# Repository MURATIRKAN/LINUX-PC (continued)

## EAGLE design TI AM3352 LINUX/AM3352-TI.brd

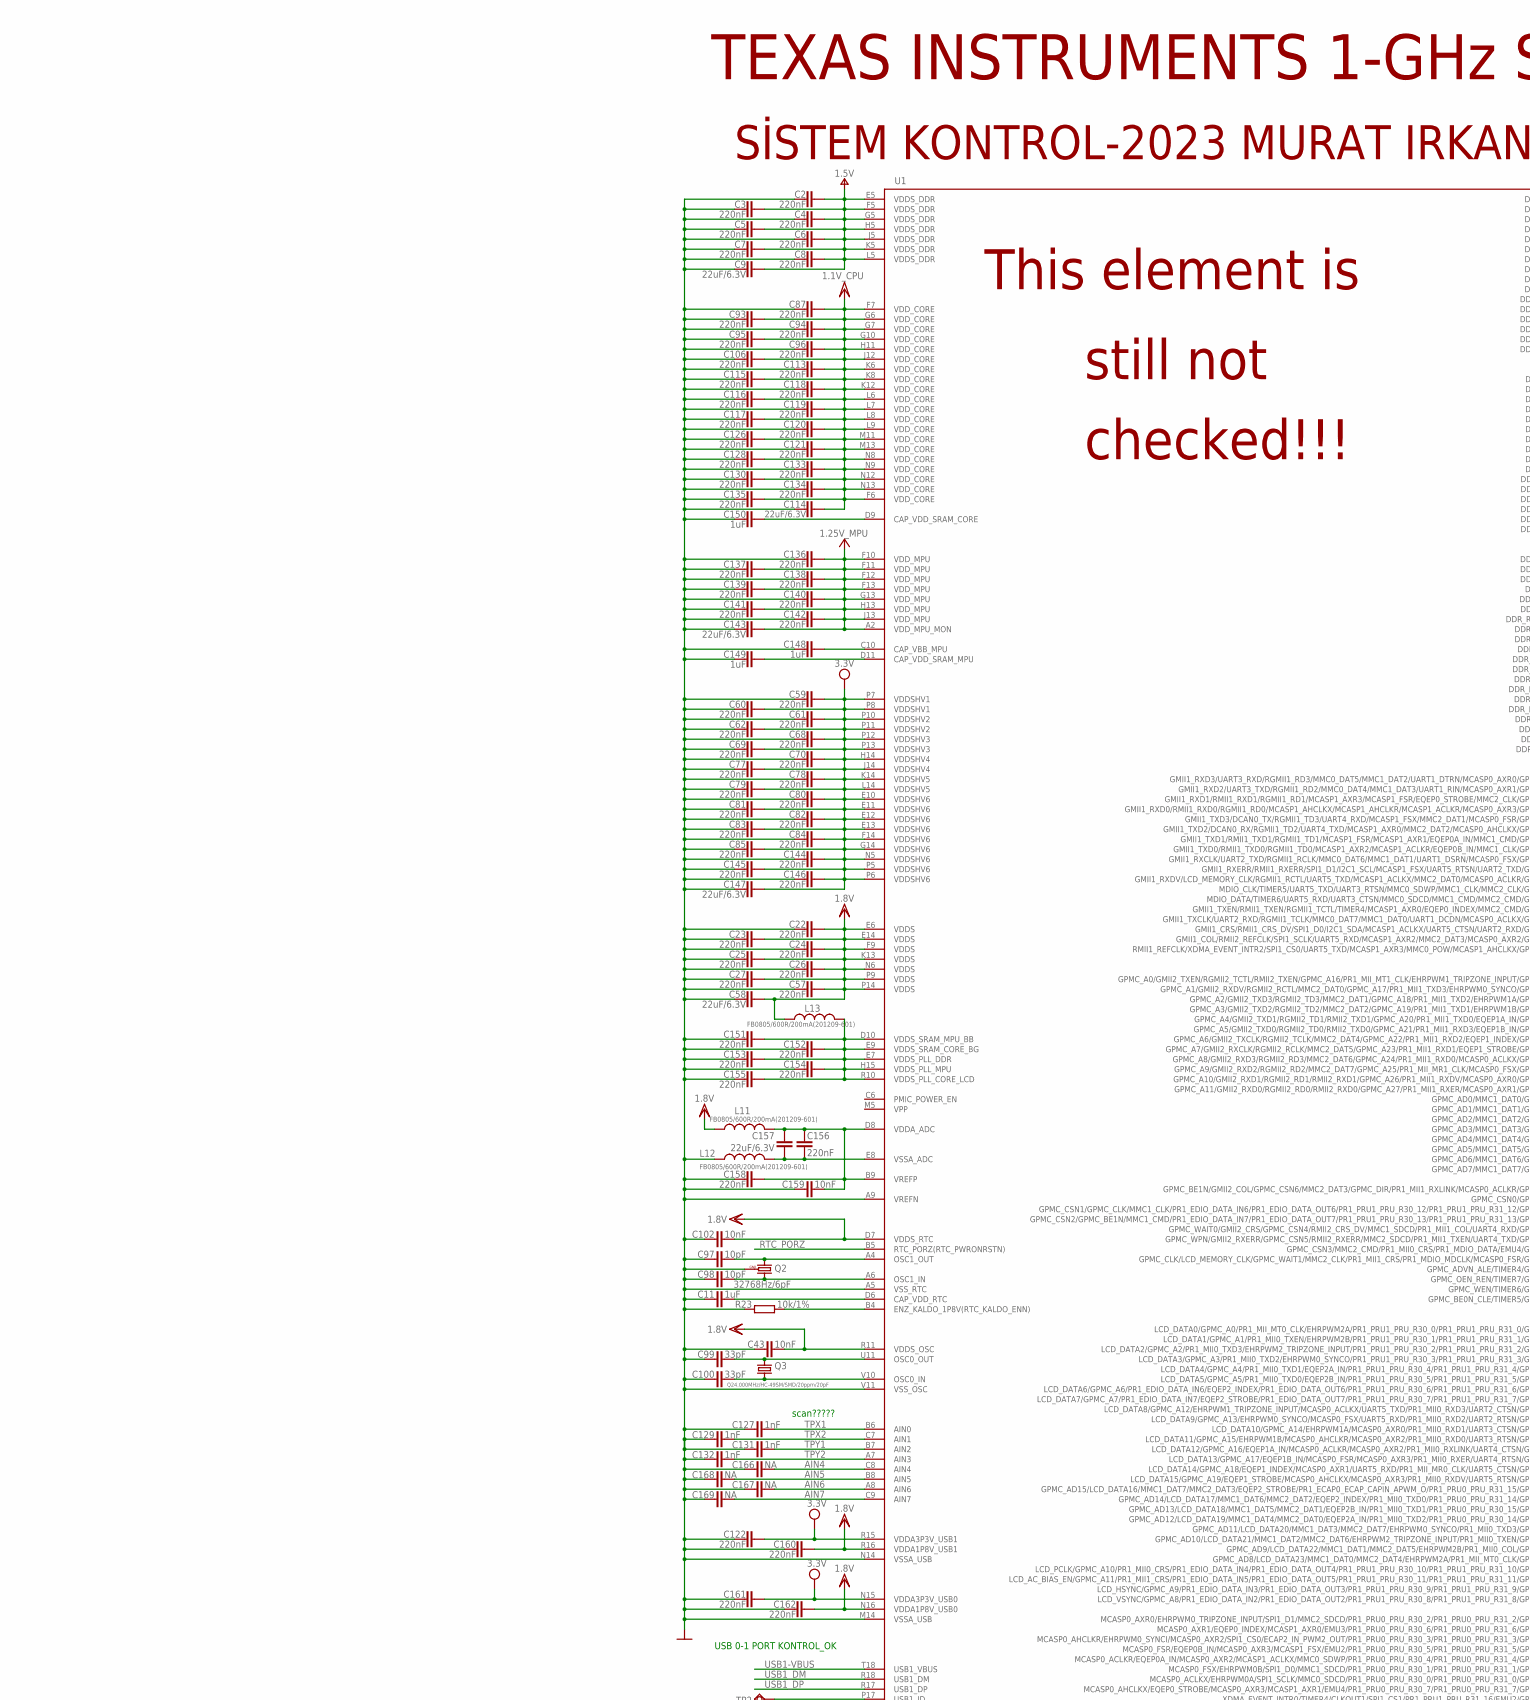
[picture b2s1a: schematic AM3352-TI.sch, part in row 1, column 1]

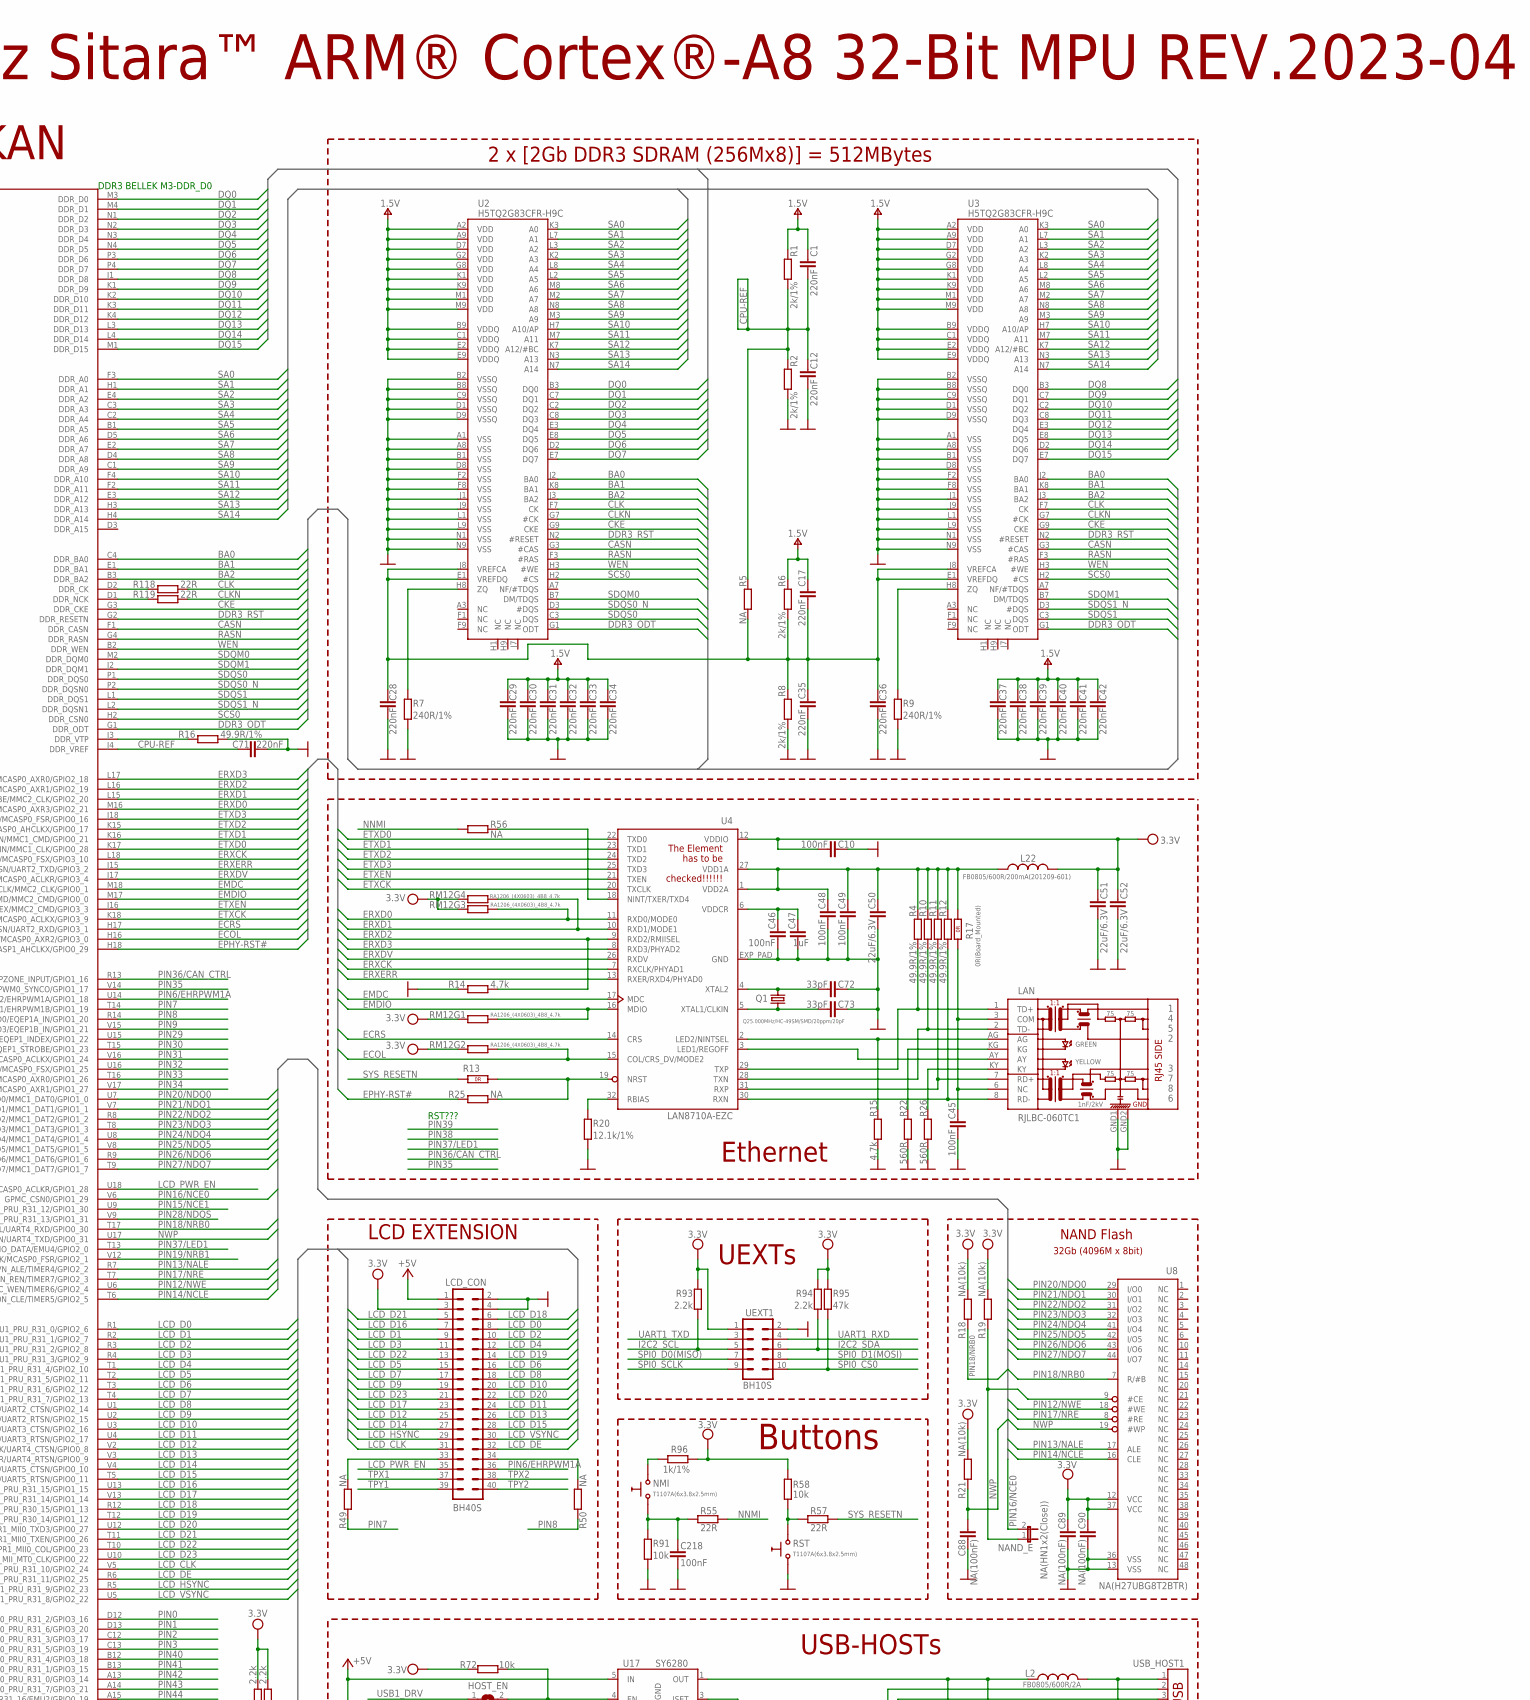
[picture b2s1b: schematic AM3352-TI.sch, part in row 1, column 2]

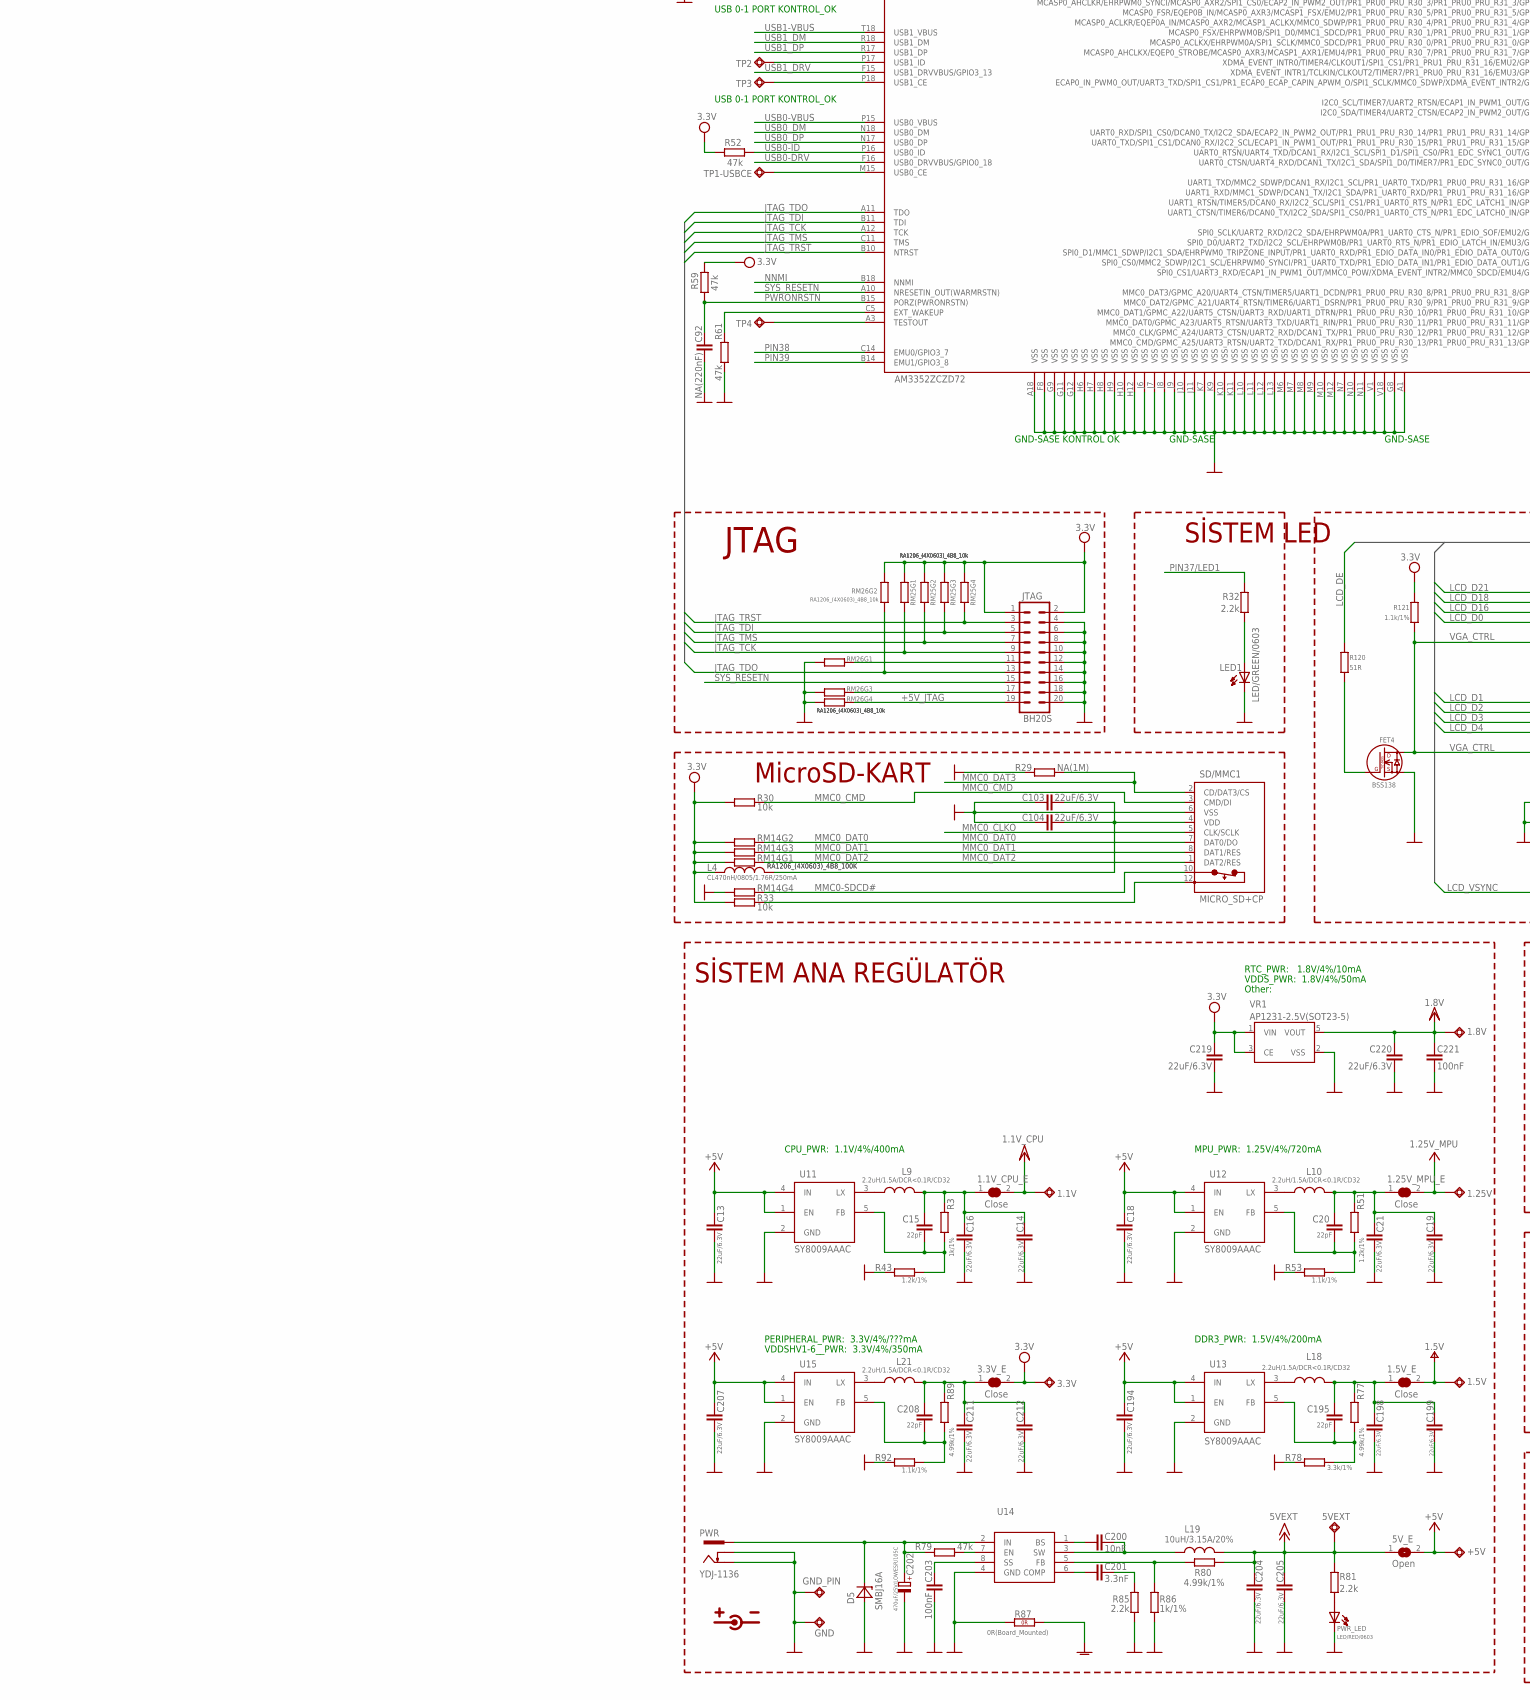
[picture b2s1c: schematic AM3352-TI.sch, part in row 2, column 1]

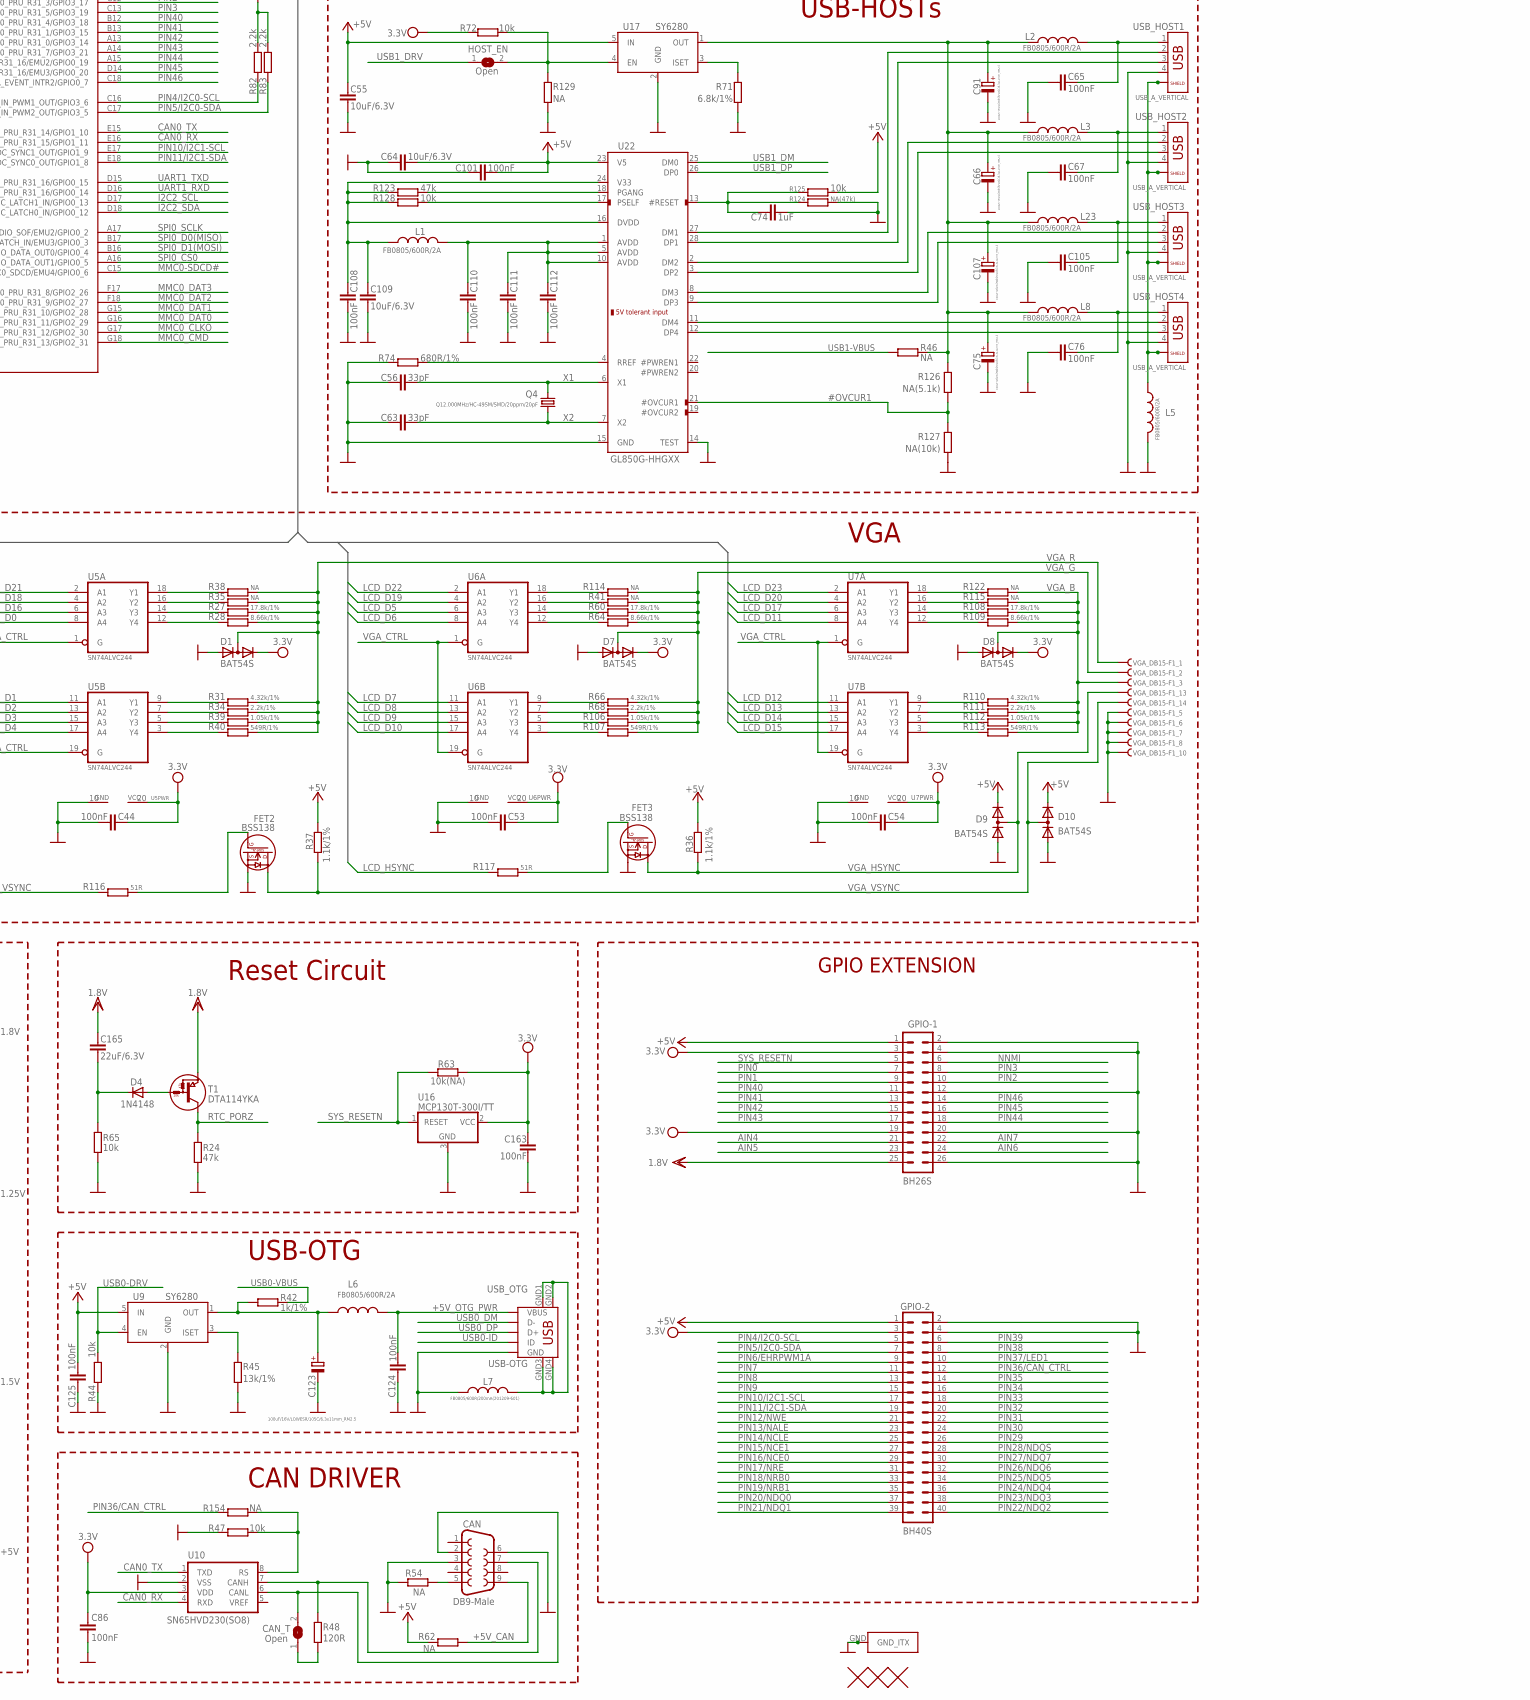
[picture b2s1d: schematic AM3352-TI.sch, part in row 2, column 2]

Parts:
1.1V, 1.5V, 1.8V, 1.25V, 3.3V, 5VEXT: TESTPADTESTPAD_40-ROUND; TESTPAD_40-ROUND
1.1V_CPU_E, 1.5V_E, 1.25V_MPU_E, 3.3V_E: Close; SJ_1_SMALLER_CLOSE
5V_E: Open; SJ_1_SMALLER
+5V: TESTPADTESTPAD_40-ROUND; TESTPAD_40-ROUND
C1, C2, C3, C4, C5, C6, C7, C8, C12, C17, C22, C23, C24, C25, C26, C27, C28, C29, C30, C31, C32, C33, C34, C35, C36, C37, C38, C39, C40, C41, C42, C57, C59, C60, C61, C62, C68, C69, C70, C71, C77, C78, C79, C80, C81, C82, C83, C84, C85, C87, C93, C94, C95, C96, C106, C113, C115, C116, C117, C118, C119, C120, C121, C122, C126, C128, C130, C133, C134, C135, C136, C137, C138, C139, C140, C141, C142, C144, C145, C146, C151, C152, C153, C154, C155, C156, C158, C160, C161, C162: 220nF; C0603_DWS
C9, C13, C14, C16, C18, C19, C21, C50, C51, C52, C58, C103, C104, C114, C143, C147, C157, C165, C194, C198, C199, C204, C205, C207, C211, C212, C219, C220: 22uF/6.3V; C0603_DWS
C10, C44, C45, C46, C48, C49, C53, C54, C65, C67, C76, C86, C101, C105, C108, C110, C111, C112, C124, C125, C163, C203, C218, C221: 100nF; C0603_DWS
C11, C47, C74, C148, C149, C150: 1uF; C0603_DWS
C15, C20, C195, C208: 22pF; C0603_DWS
C43, C102, C159, C200: 10nF; C0603_DWS
C55, C64, C109: 10uF/6.3V; C0603_DWS
C56, C63, C72, C73, C99, C100: 33pF; C0603_DWS
C66, C75, C91, C107, C123: 100uF/16V/LOWESR/105C/6.3x11mm_RM2.5; E2,5-6,3
C88, C89, C90: NA(100nF); C0603_DWS
C92: NA(220nF); C0603_DWS
C97, C98: 10pF; C0603_DWS
C127, C129, C131, C132: 1nF; C0603_DWS
C166, C167, C168, C169: NA; C0603_DWS
C201: 3.3nF; C0603_DWS
C202: 470uF/25V/LOWESR/105C; E5-10,5
CAN: DB9-Male; F09HP-MALE
CAN_T: Open; SJ
D1, D7, D8, D9, D10: BAT54S; SOT23C(BAT54S)
D4: 1N4148; MELF-MLL41
D5: SMBJ16A; DO214AA
FET2, FET3, FET4: BSS138; SOT23
GND: TESTPADTESTPAD_40-ROUND; TESTPAD_40-ROUND
GND_PIN: TESTPAD3; TEST_PAD40/70/SQUARE
GPIO-1: BH26S; ML26
GPIO-2: BH40S; ML40
HOST_EN: Open; SJ_1_SMALLER
JTAG: BH20S; ML20-MALE
L1, L2, L3, L5, L6, L8, L23: FB0805/600R/2A; L0805_5MIL_DWS
L4: CL470nH/0805/1.76R/250mA; L0805_5MIL_DWS
L7, L11, L12, L13, L22: FB0805/600R/200mA(201209-601); L0805_5MIL_DWS
L9, L10, L18, L21: 2.2uH/1.5A/DCR<0.1R/CD32; CD32
L19: 10uH/3.15A/20%; 8X8MM_3131
LAN: RJLBC-060TC1
LCD_CON: BH40S; ML40
LED1: LED/GREEN/0603; LED-0603
NAND_E: NA(HN1x2(Close)); JP1
NMI: T1107A(6x3.8x2.5mm); SW-TAKT_6X3.5_SMD
PWR: YDJ-1136; PWR_JACK_UNI_MILLING
PWR_LED: LED/RED/0603; LED-0603
Q1: Q25.000MHz/HC-49SM/SMD/20ppm/20pF; HC49/SMD2_THIN
Q2: 32768Hz/6pF; TC26H_3_REPAIR_SMD
Q3: Q24.000MHz/HC-49SM/SMD/20ppm/20pF; HC49/SMD2_THIN
Q4: Q12.000MHz/HC-49SM/SMD/20ppm/20pF; HC49/SMD2_THIN
R1, R2, R6, R8: 2k/1%; R0603_5MIL_DWS
R3, R42, R86, R96: 1k/1%; R0603_5MIL_DWS
R4, R10, R11, R12, R16: 49.9R/1%; R0603_5MIL_DWS
R5, R25, R35, R38, R41, R46, R49, R50, R56, R114, R115, R122, R129: NA; R0603_5MIL_DWS
R7, R9: 240R/1%; R0603_5MIL_DWS
R13: R_0R0R(NA); 0603_0R
R14, R15: 4.7k; R0603_5MIL_DWS
R17, R87: 0R(Board_Mounted); 0603_0R
R18, R19, R21, R127: NA(10k); R0603_5MIL_DWS
R20: 12.1k/1%; R0603_5MIL_DWS
R22, R26: 560R; R0603_5MIL_DWS
R23: 10k/1%; R0603_5MIL_DWS
R24, R52, R59, R61, R79, R95, R123: 47k; R0603_5MIL_DWS
R27, R60, R108: 17.8k/1%; R0603_5MIL_DWS
R28, R64, R109: 8.66k/1%; R0603_5MIL_DWS
R29: NA(1M); R0603_5MIL_DWS
R30, R33, R44, R47, R58, R65, R72, R91, R125, R128: 10k; R0603_5MIL_DWS
R31, R66, R110: 4.32k/1%; R0603_5MIL_DWS
R32, R81, R82, R83, R85, R93, R94: 2.2k; R0603_5MIL_DWS
R34, R68, R111: 2.2k/1%; R0603_5MIL_DWS
R36, R37, R53, R92, R121: 1.1k/1%; R0603_5MIL_DWS
R39, R106, R112: 1.05k/1%; R0603_5MIL_DWS
R40, R107, R113: 549R/1%; R0603_5MIL_DWS
R43, R51: 1.2k/1%; R0603_5MIL_DWS
R45: 13k/1%; R0603_5MIL_DWS
R48: 120R; R1206_5MIL_WS
R54, R62, R154: NA; R0603_5MIL_DWS_NA
R55, R57, R118, R119: 22R; R0603_5MIL_DWS
R63: 10k(NA); R0603_5MIL_DWS
R71: 6.8k/1%; R0603_5MIL_DWS
R74: 680R/1%; R0603_5MIL_DWS
R77, R80, R89: 4.99k/1%; R0603_5MIL_DWS
R78: 3.3k/1%; R0603_5MIL_DWS
R116, R117, R120: 51R; R0603_5MIL_DWS
R124: NA(47k); R0603_5MIL_DWS
R126: NA(5.1k); R0603_5MIL_DWS
RM12: RA1206_(4X0603)_4B8_4.7k; R_MATRIX_4
RM14: RA1206_(4X0603)_4B8_100K; R_MATRIX_4
RM25, RM26: RA1206_(4X0603)_4B8_10k; R_MATRIX_4
RST: T1107A(6x3.8x2.5mm); SW-TAKT_6X3.5_SMD
SD/MMC1: MICRO_SD+CP; TFR-MEM-CON
T1: DTA114YKA; SOT-23
TP1-USBCE, TP2, TP3, TP4: TESTPADTESTPAD_40-ROUND; TESTPAD_40-ROUND
U1: AM3352ZCZD72; S-PBGA-N324
U2, U3: H5TQ2G83CFR-H9C; FBGA78
U4: LAN8710A-EZC; QFN-32
U5, U6, U7: SN74ALVC244; PW
U8: NA(H27UBG8T2BTR); TSOP48
U9, U17: SY6280; SOT23-5
U10: SN65HVD230(SO8); SO-08
U11, U12, U13, U15: SY8009AAAC; SOT23-5
U14: MP1482DS; SOIC8
U16: MCP130T-300I/TT; SOT23
U19, U20, U21: FIDUCIAL1X2; FIDUCIAL-1X2
U22: GL850G-HHGXX; SSOP28
U$1: NANO_ITX_; NANO-ITX_140X140
UEXT1: BH10S; ML10-MALE
USB_HOST1, USB_HOST2, USB_HOST3, USB_HOST4: USB_A_VERTICAL; USB_A_VERTICAL_PTH
USB_OTG: USB-OTG; USB_MINI_9PIN
VGA_DB15-F1: VGA15; DB15-F_22MM
VR1: AP1231-2.5V(SOT23-5); SOT-23-5

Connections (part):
#OVCUR1: R126.1, R127.2, U22.21 (#OVCUR1)
+5V: 5V_E.2, +5V.1, C13.1, C18.1, C55.1, C64.1, C101.1, C125.1, C194.1, C207.1, D9.2 (K), D10.2 (K), GPIO-1.1, GPIO-2.1, LCD_CON.1, R36.2, R37.2, R62.1, R125.2, U9.5 (IN), U11.1 (EN), U11.4 (IN), U12.1 (EN), U12.4 (IN), U13.1 (EN), U13.4 (IN), U15.1 (EN), U15.4 (IN), U17.5 (IN), U22.23 (V5)
+5V_CAN: CAN.9, R62.2
+5V_JTAG: JTAG.19, RM26.4.2 (2)
+5V_OTG_PWR: C124.1, L6.1, USB_OTG.VBUS
+15V: 5VEXT.1, 5V_E.1, C204.1, C205.1, L19.2, R80.2, R81.1
AIN4: C166.2, GPIO-1.21, U1.C8 (AIN4)
AIN5: C168.2, GPIO-1.23, U1.B8 (AIN5)
AIN6: C167.2, GPIO-1.24, U1.A8 (AIN6)
AIN7: C169.2, GPIO-1.22, U1.C9 (AIN7)
AVDD1: C110.1, C111.1, C112.1, L1.2, U22.1 (AVDD), U22.5 (AVDD), U22.10 (AVDD)
BA0: U1.C4 (DDR_BA0), U2.J2 (BA0), U3.J2 (BA0)
BA1: U1.E1 (DDR_BA1), U2.K8 (BA1), U3.K8 (BA1)
BA2: U1.B3 (DDR_BA2), U2.J3 (BA2), U3.J3 (BA2)
CAN0_RX: U1.E16 (UART0_TXD/SPI1_CS1/DCAN0_RX/I2C2_SCL/EC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), U10.4 (RXD)
CAN0_TX: U1.E15 (UART0_RXD/SPI1_CS0/DCAN0_TX/I2C2_SDA/EC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), U10.1 (TXD)
CANH: CAN.7, R48.2, U10.7 (CANH)
CANL: CAN.2, CAN_T.2, U10.6 (CANL)
CASN: U1.F1 (DDR_CASN), U2.G3 (#CAS), U3.G3 (#CAS)
CKE: U1.G3 (DDR_CKE), U2.G9 (CKE), U3.G9 (CKE)
CLK: R118.1, U2.F7 (CK), U3.F7 (CK)
CLKN: R119.1, U2.G7 (#CK), U3.G7 (#CK)
CPU-REF: C1.2, C12.2, C71.2, R1.1, R2.2, R5.2, U1.J4 (DDR_VREF)
DDR3_ODT: U1.G1 (DDR_ODT), U2.G1 (ODT), U3.G1 (ODT)
DDR3_RST: U1.G2 (DDR_RESETN), U2.N2 (#RESET), U3.N2 (#RESET)
DM1: U22.27 (DM1), USB_HOST1.2
DM2: U22.2 (DM2), USB_HOST2.2
DM3: U22.8 (DM3), USB_HOST3.2
DM4: U22.11 (DM4), USB_HOST4.2
DP1: U22.28 (DP1), USB_HOST1.3
DP2: U22.3 (DP2), USB_HOST2.3
DP3: U22.9 (DP3), USB_HOST3.3
DP4: U22.12 (DP4), USB_HOST4.3
DQ0: U1.M3 (DDR_D0), U2.B3 (DQ0)
DQ1: U1.M4 (DDR_D1), U2.C7 (DQ1)
DQ2: U1.N1 (DDR_D2), U2.C2 (DQ2)
DQ3: U1.N2 (DDR_D3), U2.C8 (DQ3)
DQ4: U1.N3 (DDR_D4), U2.E3 (DQ4)
DQ5: U1.N4 (DDR_D5), U2.E8 (DQ5)
DQ6: U1.P3 (DDR_D6), U2.D2 (DQ6)
DQ7: U1.P4 (DDR_D7), U2.E7 (DQ7)
DQ8: U1.J1 (DDR_D8), U3.B3 (DQ0)
DQ9: U1.K1 (DDR_D9), U3.C7 (DQ1)
DQ10: U1.K2 (DDR_D10), U3.C2 (DQ2)
DQ11: U1.K3 (DDR_D11), U3.C8 (DQ3)
DQ12: U1.K4 (DDR_D12), U3.E3 (DQ4)
DQ13: U1.L3 (DDR_D13), U3.E8 (DQ5)
DQ14: U1.L4 (DDR_D14), U3.D2 (DQ6)
DQ15: U1.M1 (DDR_D15), U3.E7 (DQ7)
DRAM-REF: C17.2, C28.2, C35.2, C36.2, R5.1, R6.1, R8.2, U2.E1 (VREFDQ), U2.J8 (VREFCA), U3.E1 (VREFDQ), U3.J8 (VREFCA)
DVDD1: C108.1, C109.1, L1.1, R123.1, R128.1, U22.16 (DVDD), U22.24 (V33)
ECOL: RM12.2.2 (2), U1.H16 (GMII1_COL/RMII2_REFCLK/SPI1_SCLK/UART5_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), U4.15 (COL/CRS_DV/MODE2)
ECRS: U1.H17 (GMII1_CRS/RMII1_CRS_DV/SPI1_D0/I2C1_SDA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), U4.14 (CRS)
EMDC: U1.M18 (MDIO_CLK/TIMER5/UART5_TXD/UART3_RTSN/MM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), U4.17 (MDC)
EMDIO: RM12.1.2 (2), U1.M17 (MDIO_DATA/TIMER6/UART5_RXD/UART3_CTSN/M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), U4.16 (MDIO)
EPHY-RST#: R25.1, U1.H18 (RMII1_REFCLK/XDMA_EVENT_INTR2/SPI1_CS0/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)
ERXCK: U1.L18 (GMII1_RXCLK/UART2_TXD/RGMII1_RCLK/MMC0_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), U4.7 (RXCLK/PHYAD1)
ERXD0: RM12.3.2 (2), U1.M16 (GMII1_RXD0/RMII1_RXD0/RGMII1_RD0/MCASP1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), U4.11 (RXD0/MODE0)
ERXD1: RM12.4.2 (2), U1.L15 (GMII1_RXD1/RMII1_RXD1/RGMII1_RD1/MCASP1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), U4.10 (RXD1/MODE1)
ERXD2: R14.2, U1.L16 (GMII1_RXD2/UART3_TXD/RGMII1_RD2/MMC0_DA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), U4.9 (RXD2/RMIISEL)
ERXD3: U1.L17 (GMII1_RXD3/UART3_RXD/RGMII1_RD3/MMC0_DA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), U4.8 (RXD3/PHYAD2)
ERXDV: U1.J17 (GMII1_RXDV/LCD_MEMORY_CLK/RGMII1_RCTL/U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), U4.26 (RXDV)
ERXERR: U1.J15 (GMII1_RXERR/RMII1_RXERR/SPI1_D1/I2C1_SC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), U4.13 (RXER/RXD4/PHYAD0)
ETXCK: U1.K18 (GMII1_TXCLK/UART2_RXD/RGMII1_TCLK/MMC0_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), U4.20 (TXCLK)
ETXD0: U1.K17 (GMII1_TXD0/RMII1_TXD0/RGMII1_TD0/MCASP1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), U4.22 (TXD0)
ETXD1: U1.K16 (GMII1_TXD1/RMII1_TXD1/RGMII1_TD1/MCASP1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), U4.23 (TXD1)
ETXD2: U1.K15 (GMII1_TXD2/DCAN0_RX/RGMII1_TD2/UART4_TX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), U4.24 (TXD2)
ETXD3: U1.J18 (GMII1_TXD3/DCAN0_TX/RGMII1_TD3/UART4_RX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), U4.25 (TXD3)
ETXEN: U1.J16 (GMII1_TXEN/RMII1_TXEN/RGMII1_TCTL/TIMER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), U4.21 (TXEN)
GND: C2.1, C3.1, C4.1, C5.1, C6.1, C7.1, C8.1, C9.1, C10.1, C11.1, C12.1, C13.2, C14.2, C16.2, C18.2, C19.2, C21.2, C22.1, C23.1, C24.1, C25.1, C26.1, C27.1, C28.1, C29.1, C30.1, C31.1, C32.1, C33.1, C34.1, C35.1, C36.1, C37.1, C38.1, C39.1, C40.1, C41.1, C42.1, C43.1, C44.2, C45.1, C46.1, C47.1, C48.1, C49.1, C50.1, C51.1, C52.1, C53.2, C54.2, C55.2, C56.1, C57.1, C58.1, C59.1, C60.1, C61.1, C62.1, C63.1, C64.2, C65.2, C66.-, C67.2, C68.1, C69.1, C70.1, C71.1, C72.1, C73.1, C74.1, C75.-, C76.2, C77.1, C78.1, C79.1, C80.1, C81.1, C82.1, C83.1, C84.1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
GNDA: R87.2 (1.2)
I2C2_SCL: R93.1, U1.D17 (UART1_RTSN/TIMER5/DCAN0_RX/I2C2_SCL/SPI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), UEXT1.5
I2C2_SDA: R94.1, U1.D18 (UART1_CTSN/TIMER6/DCAN0_TX/I2C2_SDA/SPI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), UEXT1.6
JTAG_TCK: JTAG.9, RM25.1.1 (1), U1.A12 (TCK)
JTAG_TDI: JTAG.5, RM25.3.1 (1), U1.B11 (TDI)
JTAG_TDO: JTAG.13, RM26.2.2 (2), U1.A11 (TDO)
JTAG_TMS: JTAG.7, RM25.2.1 (1), U1.C11 (TMS)
JTAG_TRST: JTAG.3, RM25.4.1 (1), U1.B10 (NTRST)
LCD_CLK: LCD_CON.31, U1.V5 (LCD_PCLK/GPMC_A10/PR1_MII0_CRS/PR1_EDIO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)
LCD_D0: LCD_CON.8, U1.R1 (LCD_DATA0/GPMC_A0/PR1_MII_MT0_CLK/EHRPW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), U5.8 (A4)
LCD_D1: LCD_CON.9, U1.R2 (LCD_DATA1/GPMC_A1/PR1_MII0_TXEN/EHRPWM2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), U5.11 (A1)
LCD_D2: LCD_CON.10, U1.R3 (LCD_DATA2/GPMC_A2/PR1_MII0_TXD3/EHRPWM2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), U5.13 (A2)
LCD_D3: LCD_CON.11, U1.R4 (LCD_DATA3/GPMC_A3/PR1_MII0_TXD2/EHRPWM0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), U5.15 (A3)
LCD_D4: LCD_CON.12, U1.T1 (LCD_DATA4/GPMC_A4/PR1_MII0_TXD1/EQEP2A_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), U5.17 (A4)
LCD_D5: LCD_CON.15, U1.T2 (LCD_DATA5/GPMC_A5/PR1_MII0_TXD0/EQEP2B_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), U6.6 (A3)
LCD_D6: LCD_CON.16, U1.T3 (LCD_DATA6/GPMC_A6/PR1_EDIO_DATA_IN6/EQE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), U6.8 (A4)
LCD_D7: LCD_CON.17, U1.T4 (LCD_DATA7/GPMC_A7/PR1_EDIO_DATA_IN7/EQE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), U6.11 (A1)
LCD_D8: LCD_CON.18, U1.U1 (LCD_DATA8/GPMC_A12/EHRPWM1_TRIPZONE_INP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), U6.13 (A2)
LCD_D9: LCD_CON.19, U1.U2 (LCD_DATA9/GPMC_A13/EHRPWM0_SYNCO/MCASP0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), U6.15 (A3)
LCD_D10: LCD_CON.20, U1.U3 (LCD_DATA10/GPMC_A14/EHRPWM1A/MCASP0_AXR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), U6.17 (A4)
LCD_D11: LCD_CON.24, U1.U4 (LCD_DATA11/GPMC_A15/EHRPWM1B/MCASP0_AHC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), U7.8 (A4)
LCD_D12: LCD_CON.25, U1.V2 (LCD_DATA12/GPMC_A16/EQEP1A_IN/MCASP0_AC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), U7.11 (A1)
LCD_D13: LCD_CON.26, U1.V3 (LCD_DATA13/GPMC_A17/EQEP1B_IN/MCASP0_FS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), U7.13 (A2)
LCD_D14: LCD_CON.27, U1.V4 (LCD_DATA14/GPMC_A18/EQEP1_INDEX/MCASP0_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), U7.15 (A3)
LCD_D15: LCD_CON.28, U1.T5 (LCD_DATA15/GPMC_A19/EQEP1_STROBE/MCASP0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), U7.17 (A4)
LCD_D16: LCD_CON.7, U1.U13 (GPMC_AD15/LCD_DATA16/MMC1_DAT7/MMC2_DAT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), U5.6 (A3)
LCD_D17: LCD_CON.23, U1.V13 (GPMC_AD14/LCD_DATA17/MMC1_DAT6/MMC2_DAT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), U7.6 (A3)
LCD_D18: LCD_CON.6, U1.R12 (GPMC_AD13/LCD_DATA18/MMC1_DAT5/MMC2_DAT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), U5.4 (A2)
LCD_D19: LCD_CON.14, U1.T12 (GPMC_AD12/LCD_DATA19/MMC1_DAT4/MMC2_DAT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), U6.4 (A2)
LCD_D20: LCD_CON.22, U1.U12 (GPMC_AD11/LCD_DATA20/MMC1_DAT3/MMC2_DAT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), U7.4 (A2)
LCD_D21: LCD_CON.5, U1.T11 (GPMC_AD10/LCD_DATA21/MMC1_DAT2/MMC2_DAT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), U5.2 (A1)
LCD_D22: LCD_CON.13, U1.T10 (GPMC_AD9/LCD_DATA22/MMC1_DAT1/MMC2_DAT5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), U6.2 (A1)
LCD_D23: LCD_CON.21, U1.U10 (GPMC_AD8/LCD_DATA23/MMC1_DAT0/MMC2_DAT4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), U7.2 (A1)
LCD_DE: LCD_CON.32, R120.1, U1.R6 (LCD_AC_BIAS_EN/GPMC_A11/PR1_MII1_CRS/PR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)
LCD_HSYNC: LCD_CON.29, R117.1, U1.R5 (LCD_HSYNC/GPMC_A9/PR1_EDIO_DATA_IN3/PR1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)
LCD_PWR_EN: LCD_CON.35, U1.U18 (GPMC_BE1N/GMII2_COL/GPMC_CSN6/MMC2_DAT3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)
LCD_VSYNC: LCD_CON.30, R116.1, U1.U5 (LCD_VSYNC/GPMC_A8/PR1_EDIO_DATA_IN2/PR1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)
MMC0-SDCD#: RM14.4.2 (2), SD/MMC1.10 (CP_E), U1.C15 (SPI0_CS1/UART3_RXD/ECAP1_IN_PWM1_OUT/MM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)
MMC0_CLKO: SD/MMC1.5 (CLK/SCLK), U1.G17 (MMC0_CLK/GPMC_A24/UART3_CTSN/UART2_RXD/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)
MMC0_CMD: R30.1, SD/MMC1.3 (CMD/DI), U1.G18 (MMC0_CMD/GPMC_A25/UART3_RTSN/UART2_TXD/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)
MMC0_DAT0: RM14.2.1 (1), SD/MMC1.7 (DAT0/DO), U1.G16 (MMC0_DAT0/GPMC_A23/UART5_RTSN/UART3_TXD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)
MMC0_DAT1: RM14.3.1 (1), SD/MMC1.8 (DAT1/RES), U1.G15 (MMC0_DAT1/GPMC_A22/UART5_CTSN/UART3_RXD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)
MMC0_DAT2: RM14.1.1 (1), SD/MMC1.1 (DAT2/RES), U1.F18 (MMC0_DAT2/GPMC_A21/UART4_RTSN/TIMER6/UA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)
MMC0_DAT3: R29.1, SD/MMC1.2 (CD/DAT3/CS), U1.F17 (MMC0_DAT3/GPMC_A20/UART4_CTSN/TIMER5/UA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)
unnamed: C148.2, U1.C10 (CAP_VBB_MPU)
unnamed: R16.2, U1.J3 (DDR_VTP)
unnamed: R7.2, U2.H8 (ZQ)
unnamed: L9.1, U11.3 (LX)
unnamed: R9.2, U3.H8 (ZQ)
unnamed: R20.2, U4.32 (RBIAS)
unnamed: C11.2, U1.D6 (CAP_VDD_RTC)
unnamed: L18.1, U13.3 (LX)
unnamed: 1.1V_CPU_E.1, C14.1, C15.1, C16.1, L9.2, R3.1
unnamed: LAN.AG, R15.1, U4.2 (LED2/NINTSEL)
unnamed: C15.2, R3.2, R43.1, U11.5 (FB)
unnamed: R23.1, U1.B4 (ENZ_KALDO_1P8V(RTC_KALDO_ENN))
unnamed: L10.1, U12.3 (LX)
unnamed: C46.2, C47.2, U4.6 (VDDCR)
unnamed: TP1-USBCE.1, U1.M15 (USB0_CE)
unnamed: 1.25V_MPU_E.1, C19.1, C20.1, C21.1, L10.2, R51.1
unnamed: C48.2, C49.2, C50.2, L22.1, R4.2, R10.2, R11.2, R12.2, R17.2 (1.2), U4.1 (VDD2A), U4.27 (VDD1A)
unnamed: 1.5V_E.1, C195.1, C198.1, C199.1, L18.2, R77.1
unnamed: C195.2, R77.2, R78.1, U13.5 (FB)
unnamed: R112.1, U7.5 (Y3)
unnamed: R110.1, U7.9 (Y1)
unnamed: C20.2, R51.2, R53.1, U12.5 (FB)
unnamed: C149.2, U1.D11 (CAP_VDD_SRAM_MPU)
unnamed: R108.1, U7.14 (Y3)
unnamed: C150.2, U1.D9 (CAP_VDD_SRAM_CORE)
unnamed: C156.1, C157.1, L12.2, U1.E8 (VSSA_ADC)
unnamed: FET2.1 (G), R116.2
unnamed: C156.2, C157.2, C158.2, C159.2, L11.2, U1.B9 (VREFP), U1.D8 (VDDA_ADC)
unnamed: FET3.1 (G), R117.2
unnamed: FET4.1 (G), R120.2
unnamed: C202.+, D5.C, PWR.+, R79.1, U14.2 (IN)
unnamed: R13.2 (1.2), R25.2, U4.19 (NRST)
unnamed: R35.1, U5.16 (Y2)
unnamed: C151.2, C152.2, C153.2, C154.2, C155.2, L13.2, U1.D10 (VDDS_SRAM_MPU_BB), U1.E7 (VDDS_PLL_DDR), U1.E9 (VDDS_SRAM_CORE_BG), U1.H15 (VDDS_PLL_MPU), U1.R10 (VDDS_PLL_CORE_LCD)
unnamed: TP2.1, U1.P17 (USB1_ID)
unnamed: C203.1, U14.8 (SS)
unnamed: R79.2, U14.7 (EN)
unnamed: TP3.1, U1.P18 (USB1_CE)
unnamed: LAN.1 (TD+), R4.1, U4.29 (TXP)
unnamed: LAN.2 (TD-), R10.1, U4.28 (TXN)
unnamed: LAN.7 (RD+), R11.1, U4.31 (RXP)
unnamed: R71.2, U17.3 (ISET)
unnamed: NMI.P$2 (1), R96.1
unnamed: C218.1, NMI.P$1 (0), R55.2, R91.1
unnamed: LAN.8 (RD-), R12.1, U4.30 (RXN)
unnamed: C200.1, U14.1 (BS)
unnamed: R38.1, U5.18 (Y1)
unnamed: R56.2, U4.18 (NINT/TXER/TXD4)
unnamed: R41.1, U6.16 (Y2)
unnamed: C200.2, L19.1, U14.3 (SW)
unnamed: R114.1, U6.18 (Y1)
unnamed: R115.1, U7.16 (Y2)
unnamed: LAN.KG, R22.1
unnamed: LAN.AY, U4.3 (LED1/REGOFF)
unnamed: R122.1, U7.18 (Y1)
unnamed: C45.2, LAN.3 (COM), LAN.6 (NC), R17.1 (1.1)
unnamed: LAN.KY, R26.1
unnamed: R33.1, SD/MMC1.12 (PACK)
unnamed: R61.2, U1.C5 (EXT_WAKEUP)
unnamed: C201.1, U14.6 (COMP)
unnamed: C201.2, R85.1
unnamed: R80.1, R86.1, U14.5 (FB)
unnamed: R57.2, R58.1, RST.P$2 (1)
unnamed: L21.1, U15.3 (LX)
unnamed: 3.3V_E.1, C208.1, C211.1, C212.1, L21.2, R89.1
unnamed: C208.2, R89.2, R92.1, U15.5 (FB)
unnamed: R74.2, U22.4 (RREF)
unnamed: R123.2, U22.18 (PGANG)
unnamed: TP4.1, U1.A3 (TESTOUT)
unnamed: D4.2 (A), T1.1 (B)
unnamed: C165.2, D4.1 (C), R65.1
unnamed: L5.2, USB_HOST1.P$3 (5), USB_HOST1.P$4 (6), USB_HOST2.P$3 (5), USB_HOST2.P$4 (6), USB_HOST3.P$3 (5), USB_HOST3.P$4 (6), USB_HOST4.P$3 (5), USB_HOST4.P$4 (6)
unnamed: C65.1, L2.2, USB_HOST1.1
unnamed: R47.1, R154.1, U10.8 (RS)
unnamed: HOST_EN.2, R72.2, R129.2, U17.4 (EN)
unnamed: C76.1, L8.2, USB_HOST4.1
unnamed: C66.+, C75.+, C91.+, C107.+, L2.1, L3.1, L8.1, L23.1, R46.2, R126.2, U17.1 (OUT)
unnamed: CAN.5, R54.2
unnamed: C97.2, Q2.1, U1.A4 (OSC1_OUT)
unnamed: R45.2, U9.3 (ISET)
unnamed: C123.+, L6.2, R42.2, U9.1 (OUT)
unnamed: R113.1, U7.3 (Y4)
unnamed: R128.2, U22.17 (PSELF)
unnamed: R111.1, U7.7 (Y2)
unnamed: R109.1, U7.12 (Y4)
unnamed: C67.1, L3.2, USB_HOST2.1
unnamed: C105.1, L23.2, USB_HOST3.1
unnamed: C98.2, Q2.2, U1.A6 (OSC1_IN)
unnamed: R66.1, U6.9 (Y1)
unnamed: R68.1, U6.7 (Y2)
unnamed: C74.2, R124.1, R125.1, U22.13 (#RESET)
unnamed: PWR_LED.A, R81.2
unnamed: R106.1, U6.5 (Y3)
unnamed: R107.1, U6.3 (Y4)
unnamed: R60.1, U6.14 (Y3)
unnamed: R64.1, U6.12 (Y4)
unnamed: R31.1, U5.9 (Y1)
unnamed: R34.1, U5.7 (Y2)
unnamed: R39.1, U5.5 (Y3)
unnamed: R40.1, U5.3 (Y4)
unnamed: R27.1, U5.14 (Y3)
unnamed: R28.1, U5.12 (Y4)
unnamed: JTAG.11, RM26.1.2 (2)
unnamed: JTAG.17, RM26.3.2 (2)
unnamed: LCD_CON.33, R49.1
unnamed: LCD_CON.34, R50.1
unnamed: LED1.A, R32.2
unnamed: NAND_E.1, R19.2, U8.9 (#CE)
unnamed: L7.2, USB_OTG.GND1, USB_OTG.GND2, USB_OTG.GND3, USB_OTG.GND4
unnamed: CAN_T.1, R48.1
NNMI: GPIO-1.6, R55.1, R56.1, U1.B18 (NNMI)
NWP: C88.2, R21.2, U1.U17 (GPMC_WPN/GMII2_RXERR/GPMC_CSN5/RMII2_RX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), U8.19 (#WP)
PIN0: GPIO-1.7, U1.D12 (MCASP0_AXR0/EHRPWM0_TRIPZONE_INPUT/SPI1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)
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
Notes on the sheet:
SİSTEM ANA REGÜLATÖR
2 x [2Gb DDR3 SDRAM (256Mx8)] = 512MBytes
MicroSD-KART
UEXTs
Buttons
USB-OTG
NAND Flash
32Gb (4096M x 8bit)
GPIO EXTENSION
LCD EXTENSION
Ethernet
JTAG
SİSTEM LED
RST???
VGA
USB-HOSTs
CAN DRIVER
CPU_PWR: 1.1V/4%/400mA
DDR3_PWR: 1.5V/4%/200mA
PERIPHERAL_PWR: 3.3V/4%/???mA
MPU_PWR: 1.25V/4%/720mA
RTC_PWR: 1.8V/4%/10mA
VDDS_PWR: 1.8V/4%/50mA
VDDSHV1-6__PWR: 3.3V/4%/350mA
Other:
scan?????
Reset Circuit
TEXAS INSTRUMENTS 1-GHz Sitara™ ARM® Cortex®-A8 32‑Bit MPU REV.2023-04
GND-SASE KONTROL OK
GND-SASE
DDR3 BELLEK M3-DDR_D0
USB 0-1 PORT KONTROL_OK
SİSTEM KONTROL-2023 MURAT IRKAN

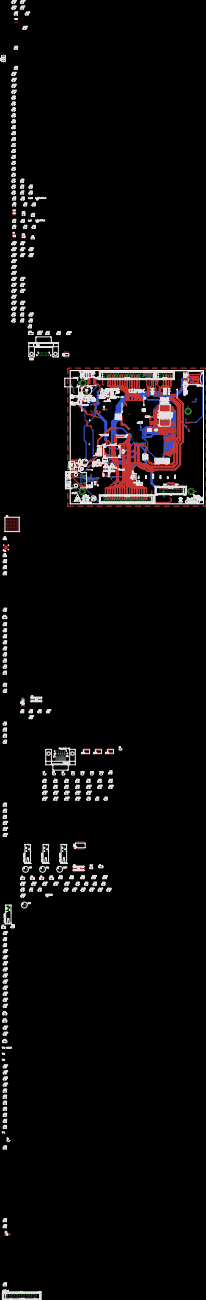
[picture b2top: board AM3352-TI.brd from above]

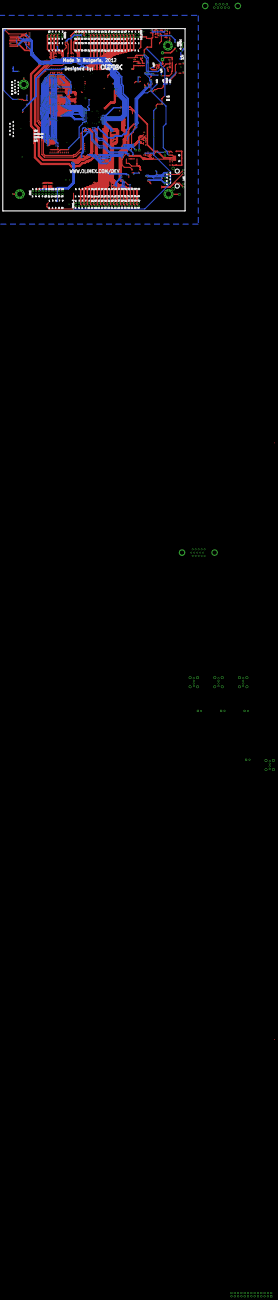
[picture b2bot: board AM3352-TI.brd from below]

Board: 4 copper layers, 139.7 x 139.7 mm, 405 parts (7 on the bottom side), 338 nets.

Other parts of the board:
U$5: LOGO-OPENHARDWARE_8X8
U$6, U$8: OLIMEX1_V
U$9: PB
U$10: ESD_SYMBOL
U$11: RECYCLE_BIN1/8
U$12: ROHS

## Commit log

2024-05-21 TEXAS INSTRUMENTS AM3352 LINUX
    REV.A
2024-05-21 BEAGLEBONE_RESİM
2024-05-21 DDR3 BELLEKLER DATASHEET
2024-05-21 BEAGLEBONE BLACK
2024-05-22 NETWORK 10/100MBIT
2024-05-22 TI AM3352 LINUX MİNİ BİLGİSAYAR
    SİSTEM KONTROL 2023-12 REV.B
    MURAT IRKAN 2023-24
2024-05-22 TI AM3352 ARM A8 LINUX MINI PC
    MURAT IRKAN 2023 -24
2024-05-23 TEXAS INSTRUMENTS AM3352 ARM A8-DEBIAN-LINUX
    MURAT IRKAN 2023-05-2024
    REV.A
2024-05-23 RK1808_USB_YAPAY ZEKA(3D TASARIM MAVİ)
2024-05-24 ROCKCHIP RK3188 MINI LINUX-PC
2024-05-24 ROCKCHIP RK3188 ANDROID&LINUX MINI-PC
    DEVRE SEMASI VE PCB REV.A
    SİSTEM TASARIM:AUTODESK EAGLE VE DIPTRACE
2024-05-31 ORANGE_PC_PLUS-2E REV.C
    MURAT IRKAN 2024-03
    ---------------------------
    ================
2024-05-31 ORNAGE PC_PLUS-2E DÖKÜMAN
    PDF DOSYASI.!
2024-06-05 ANDROID MINI PC (7.1 VE 7.0 ) ALLWINNER-H3 REV.A
    DESTEKLENEN SİSTEM: LINUX VE ANDROID 7
2024-06-05 MINI LINUX PC: ALLWINNER A10S ARM CPU
    REV.D
2024-06-10 LOKUM KONSOL/MINI PC
    ALLWINNER H3 ARM CPU
    ANDROID 7.0 7.1
    ---------------------------------
2024-06-10 ALWWINNER H3 TEKNİK DÖKÜMAN(DATASHEET)
2024-06-12 ALLWINNER A64 ARM BİLGİSAYAR
2024-06-12 LINUX SERVER ALLWINNER A20
2024-06-12 LINUX_KUTU_SOLIDWORKS-v.2018
2024-06-13 RK3328 ANDROID 12 PC-TABLET
    REFERANS TASARIM REV.A
    SİSTEM KONTROL-1
    OS:ANDROID 12
2024-06-16 RK3308 PC
2024-06-16 RK3288 GOOGLE CROMEBOOK REFERANS TASARIM DEVRESİ
2024-08-03 ORANGE PI PC PLUS
    REV.A DIPTRACE DEVRE TASARIM PRG.
2024-08-17 ORANGE PC PLUS 2E REVİZYON B.
    LINUX/ANDROID MINI PC
    -----------------------------
    MURAT IRKAN 2023/11
2024-08-17 OKUMA.md
2024-08-22 BEAGLEBONE REV.C 2023/07
    ARM A8 CPU DEBIAN LINUX (BEAGLEBONE MODİFİKASYON REV.C)
    MURAT IRKAN 2023/07
    ***********************************************************************
    3D TASARIM BEAGLEBONE BLACK - DEVRE ŞEMASI AUTODESK EAGLE
2024-08-23 DEBIAN-LINUX TI-AM3352 ARM (BEAGLEBONE BLACK)
    MURAT IRKAN TEKNİK DÖKÜMANLAR TÜMÜ EKLENDİ.!
    -----------------------------------------------------------
2024-08-24 AM3352-ARM CPU DEBIAN LINUX PC (BEAGLEBONE GİBİ)
    SİSTEM BEAGLEBONE BLACK BENZER SİSTEMDİR. 1GHz HIZINDA ARM MPU TEXAS INSTRUMENTS AM3352 İŞLEMÇİ İLE ÇALIŞIR.HYNIX LPDDR3 2GB 1866 ,2133 VEYA 1600 MH/z HIZINDA BELLEKLER KULLANIYOR.
    ANA REGÜLATÖR SİSTEMİ MODİFİKASYON LA BERABER AÇIKLAMALARI YAZDIM.DATASHEET DEKİ İŞARETLEMELER KONTROL AMAÇLIDIR.
2024-08-24 AM3352 DEBIAN LINUX BİLGİSAYAR SİSTEMİ
    HYNIX LPDDR3 1866 VEYA 2133 MH/z RAM
    VE DİĞER NETWORK KONTROL CHİP VE GÜÇ REGÜLATÖRLERİ
    İŞARETLEMELER KONTROL AMAÇLI OLARAK YAPTIM.BEAGLEBONE BLACK BENZERİ SİSTEM TASARLANDI.
2024-09-13 LOKUM_LINUX/ANDROID-PC
    ALLWINNER A64 ARM CPU (REVİZYON E)
    kicad projesi
    ---------------------------------------------------
2024-09-13 ALLWINNER-A64 ARM CPU
2024-09-13 SOLIDWORKS 3D TASARIM STEP DOSYASI
    LOKUM MINI PC 3D TASARIM ŞASE DEMO A1
2024-09-13 LOKUM-PC R1 RK3188 (ROCKCHIP)
    AUTODESK EAGLE SİSTEM DEVRE TASARIM PROGRAMI
    RK3188 REV.B MURAT IRKAN 2024-02
